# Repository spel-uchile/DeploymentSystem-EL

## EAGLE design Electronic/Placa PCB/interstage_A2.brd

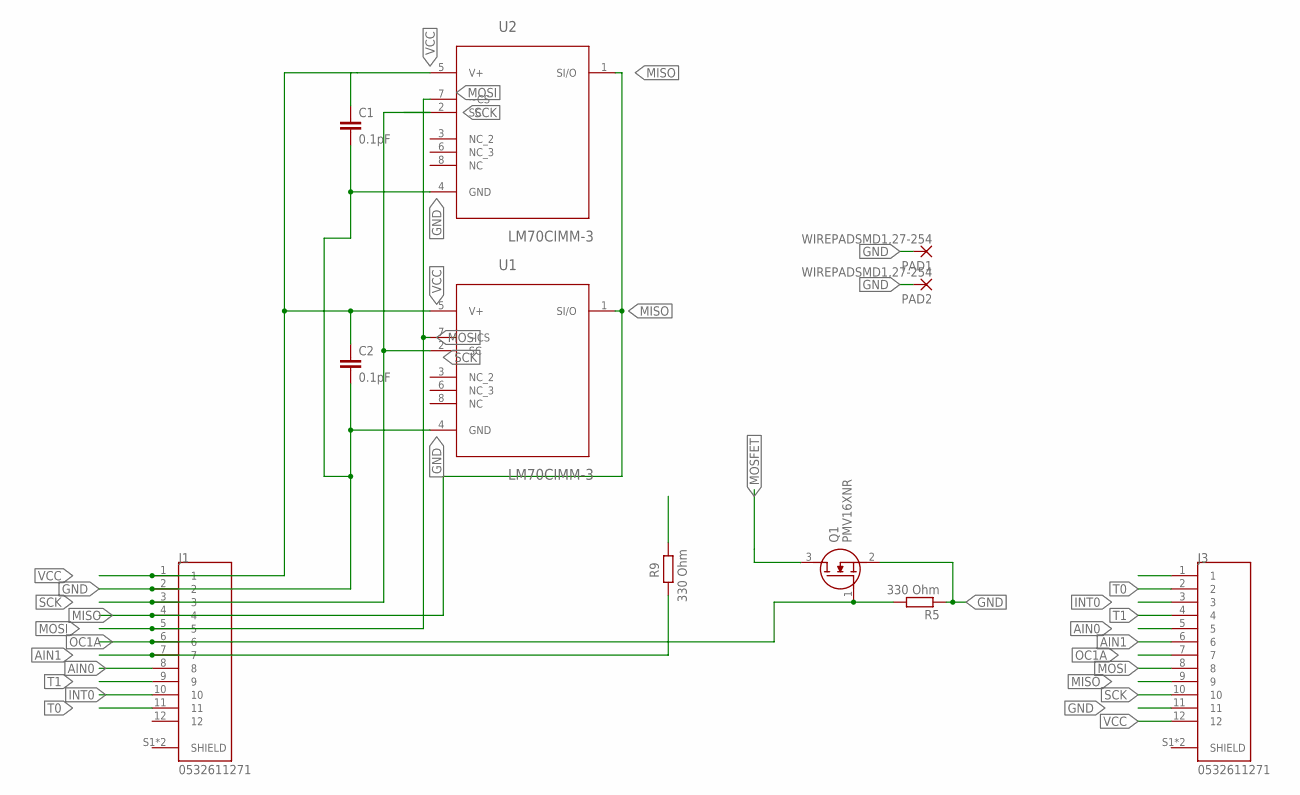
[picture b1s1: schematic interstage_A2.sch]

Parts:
C1, C2: 0.1pF; C0603K
J1, J3: 0532611271; MOLEX_0532611271
PAD1, PAD2: WIREPADSMD1,27-254; SMD1,27-2,54
Q1: PMV16XNR; SOT95P230X110-3N
R5, R9: 330 Ohm; R1206
U1, U2: LM70CIMM-3; SOP65P490X110-8N

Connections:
AIN0: J1.8, J3.5
AIN1: J1.7, J3.6, R9.2
GND: C1.2, C2.2, J1.2, J3.11, PAD1.1, PAD2.1, Q1.2 (S), R5.1, U1.4 (GND), U2.4 (GND)
INT0: J1.10, J3.3
MISO: J1.4, J3.9, U1.1 (SI/O), U2.1 (SI/O)
MOSFET: Q1.3 (D)
MOSI: J1.5, J3.8, U1.7 (~CS), U2.7 (~CS)
OC1A: J1.6, J3.7, Q1.1 (G), R5.2
SCK: J1.3, J3.10, U1.2 (SC), U2.2 (SC)
T0: J1.11, J3.2
T1: J1.9, J3.4
VCC: C1.1, C2.1, J1.1, J3.12, U1.5 (V+), U2.5 (V+)

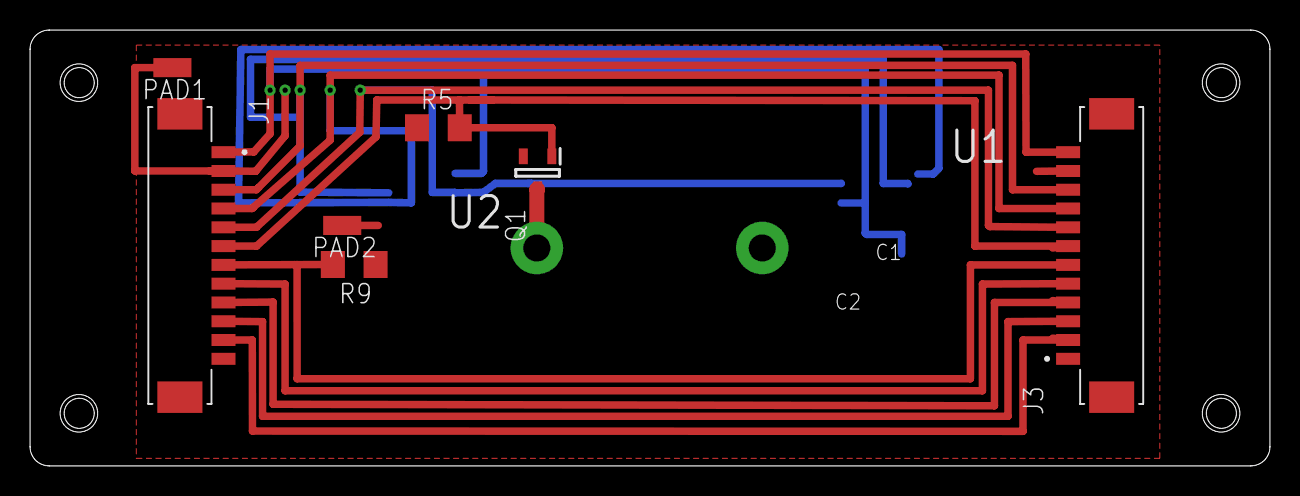
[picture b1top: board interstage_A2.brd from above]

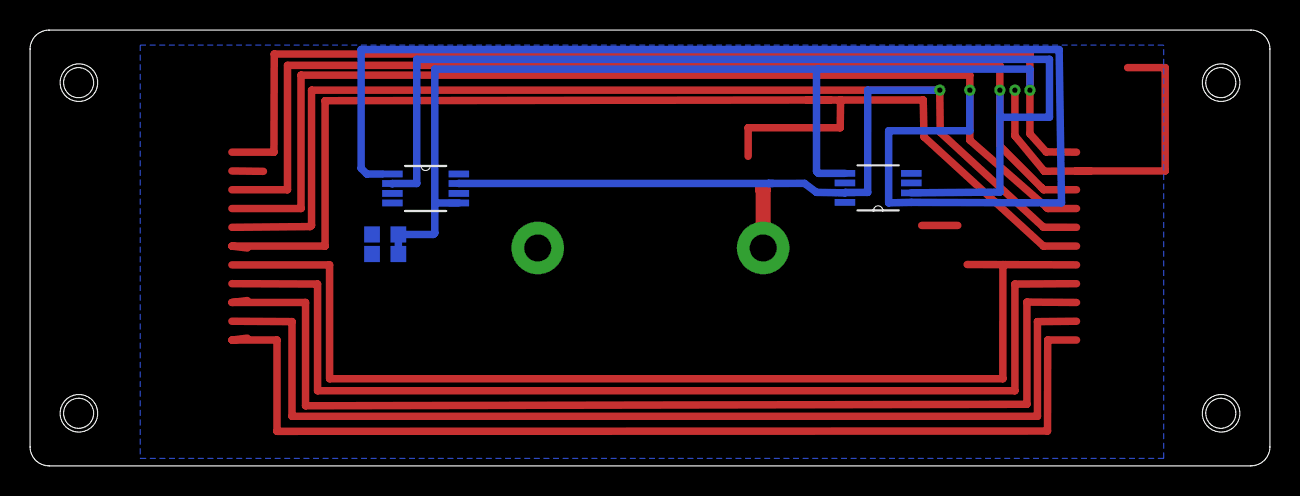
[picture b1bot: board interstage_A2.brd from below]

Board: 2 copper layers, 82.5 x 29.0 mm, 11 parts (4 on the bottom side), 11 nets.

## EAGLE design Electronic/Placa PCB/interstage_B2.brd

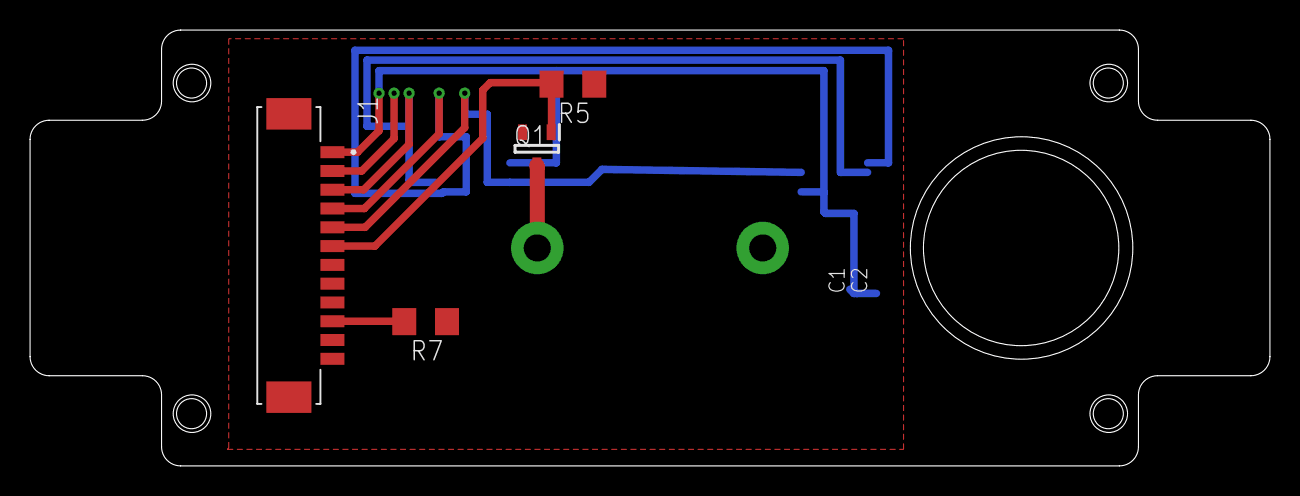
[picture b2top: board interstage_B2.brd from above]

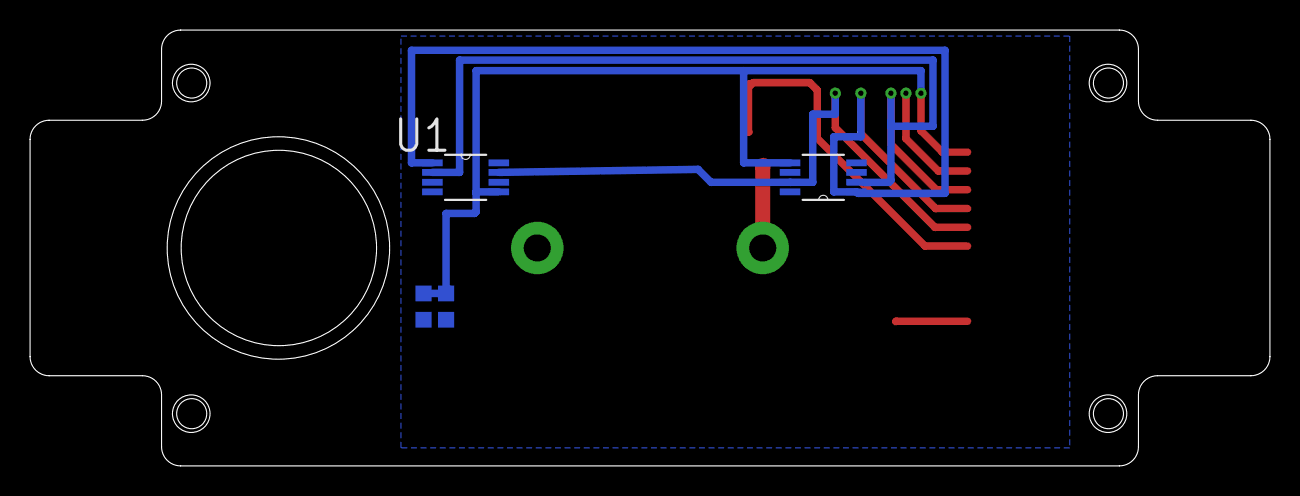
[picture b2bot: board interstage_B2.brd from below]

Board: 2 copper layers, 82.5 x 29.0 mm, 8 parts (4 on the bottom side), 7 nets.

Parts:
C1, C2: 0.1pF; C0603K
J1: 0532611271; MOLEX_0532611271
Q1: PMV16XNR; SOT95P230X110-3N
R5, R7: 330 Ohm; R1206
U1, U2: LM70CIMM-3; SOP65P490X110-8N

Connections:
GND: C1.2, C2.2, J1.2, Q1.2, R5.1, U1.4, U2.4
INT0: J1.10, R7.2
MISO: J1.4, U1.1, U2.1
MOSI: J1.5, U1.7, U2.7
OC1A: J1.6, Q1.1, R5.2
SCK: J1.3, U1.2, U2.2
VCC: C1.1, C2.1, J1.1, U1.5, U2.5

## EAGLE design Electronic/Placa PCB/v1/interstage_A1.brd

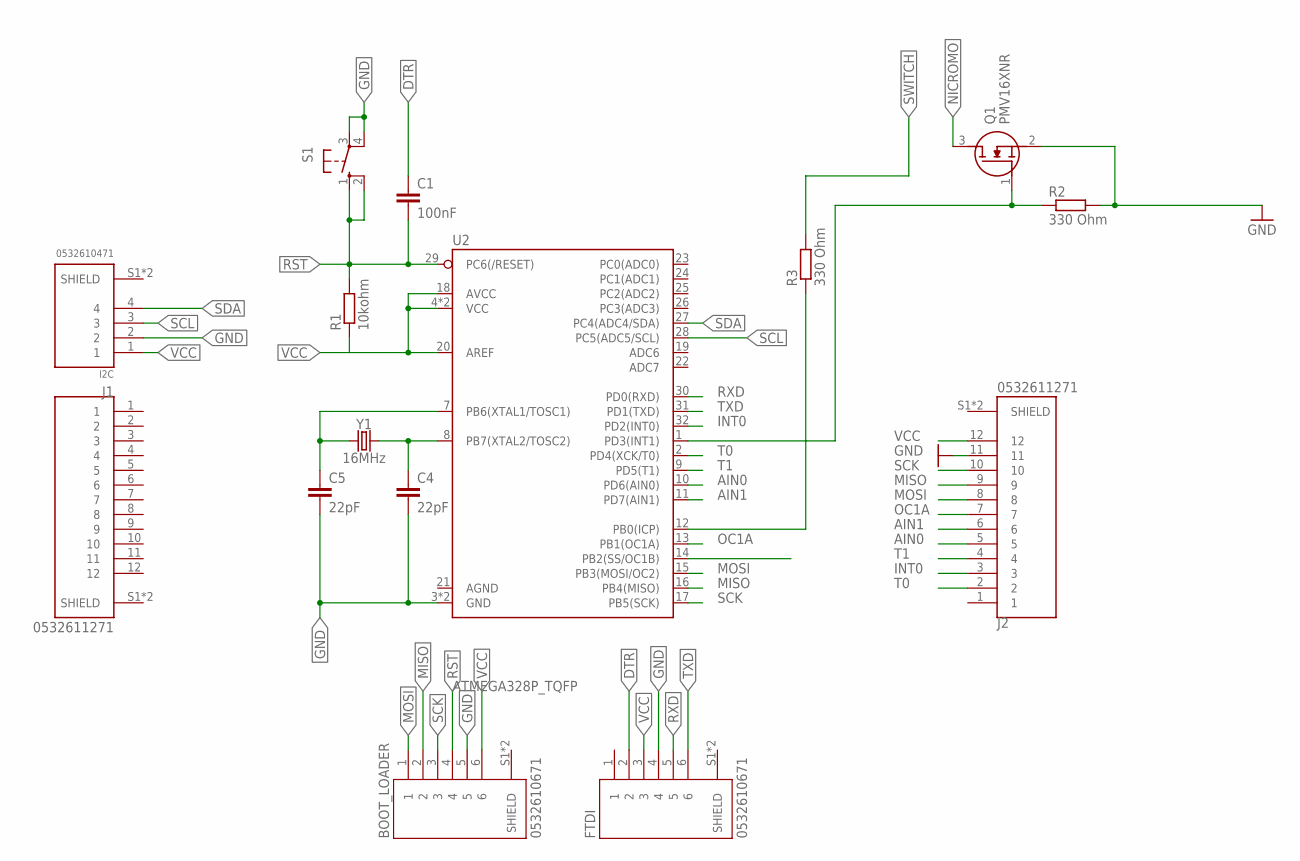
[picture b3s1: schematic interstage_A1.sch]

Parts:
BOOT_LOADER: 0532610671; MOLEX_0532610671
C1: 100nF; C0805K
C4, C5: 22pF; C0603K
FTDI: 0532610671; MOLEX_0532610671
I2C: 0532610471; MOLEX_0532610471
J1, J2: 0532611271; MOLEX_0532611271
Q1: PMV16XNR; SOT95P230X110-3N
R1: 10kohm; R1206
R2, R3: 330 Ohm; R1206
S1: 10-XX; B3F-10XX
U2: ATMEGA328P_TQFP; TQFP32-08
Y1: 16MHz; CRYSTAL-SMD-2.0X1.6MM

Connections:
AIN0: J2.5, U2.10 (PD6(AIN0))
AIN1: J2.6, U2.11 (PD7(AIN1))
DTR: C1.1, FTDI.2
GND: BOOT_LOADER.5, C4.2, C5.2, FTDI.4, I2C.2, J2.11, Q1.2 (S), R2.2, S1.3, S1.4 (P1), U2.3 (GND), U2.5 (GND)
ICP: R3.1, U2.12 (PB0(ICP))
INT0: J2.3, U2.32 (PD2(INT0))
INT1: Q1.1 (G), R2.1, U2.1 (PD3(INT1))
MISO: BOOT_LOADER.2, J2.9, U2.16 (PB4(MISO))
MOSI: BOOT_LOADER.1, J2.8, U2.15 (PB3(MOSI/OC2))
unnamed: C5.1, U2.7 (PB6(XTAL1/TOSC1)), Y1.1
unnamed: C4.1, U2.8 (PB7(XTAL2/TOSC2)), Y1.3 (2)
NICROMO: Q1.3 (D)
OC1A: J2.7, U2.13 (PB1(OC1A))
RST: BOOT_LOADER.4, C1.2, R1.2, S1.1 (S), S1.2 (S1), U2.29 (PC6(/RESET))
RXD: FTDI.5, U2.30 (PD0(RXD))
SCK: BOOT_LOADER.3, J2.10, U2.17 (PB5(SCK))
SCL: I2C.3, U2.28 (PC5(ADC5/SCL))
SDA: I2C.4, U2.27 (PC4(ADC4/SDA))
SWITCH: R3.2
T0: J2.2, U2.2 (PD4(XCK/T0))
T1: J2.4, U2.9 (PD5(T1))
TXD: FTDI.6, U2.31 (PD1(TXD))
VCC: BOOT_LOADER.6, FTDI.3, I2C.1, J2.12, R1.1, U2.4 (VCC), U2.6 (VCC), U2.18 (AVCC), U2.20 (AREF)

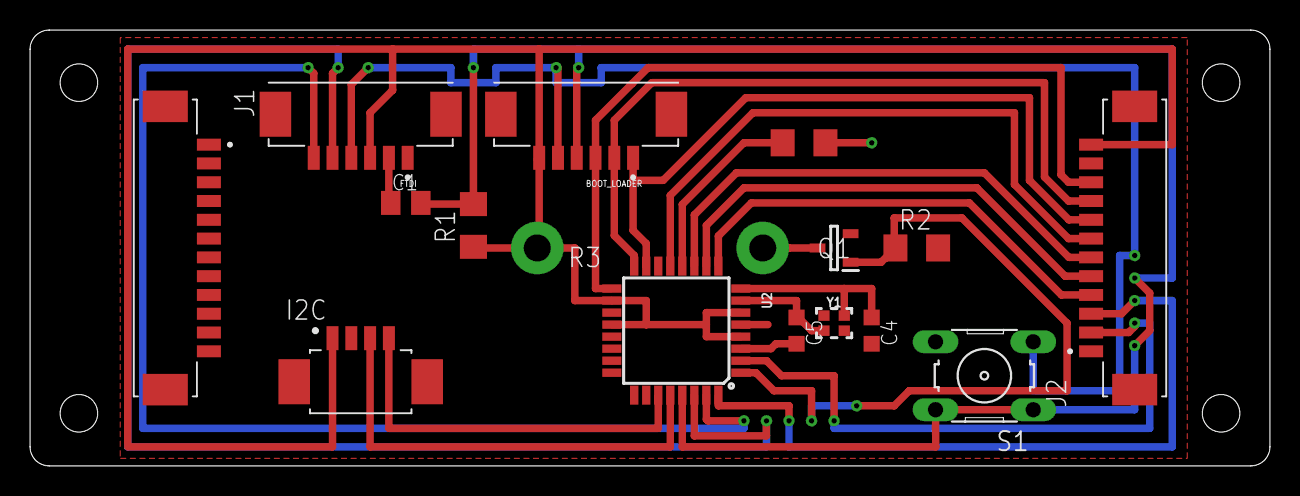
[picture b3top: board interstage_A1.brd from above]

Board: 2 copper layers, 82.5 x 29.0 mm, 15 parts (0 on the bottom side), 21 nets.

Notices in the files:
parts and their libraries:
SparkFun-IC-Microcontroller: Licensing: Creative Commons ShareAlike 4.0 International - https://creativecommons.org/licenses/by-sa/4.0
